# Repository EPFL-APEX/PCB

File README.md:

# APEX PCB's

- Every try you want to experiment in `sandbox/` pls. 
- Keep `main/` for the serious PCB's.
- Add your custom symbols and footprints in `lib/`. Make sure you've added this path to KiCAD, so it can link the libs.

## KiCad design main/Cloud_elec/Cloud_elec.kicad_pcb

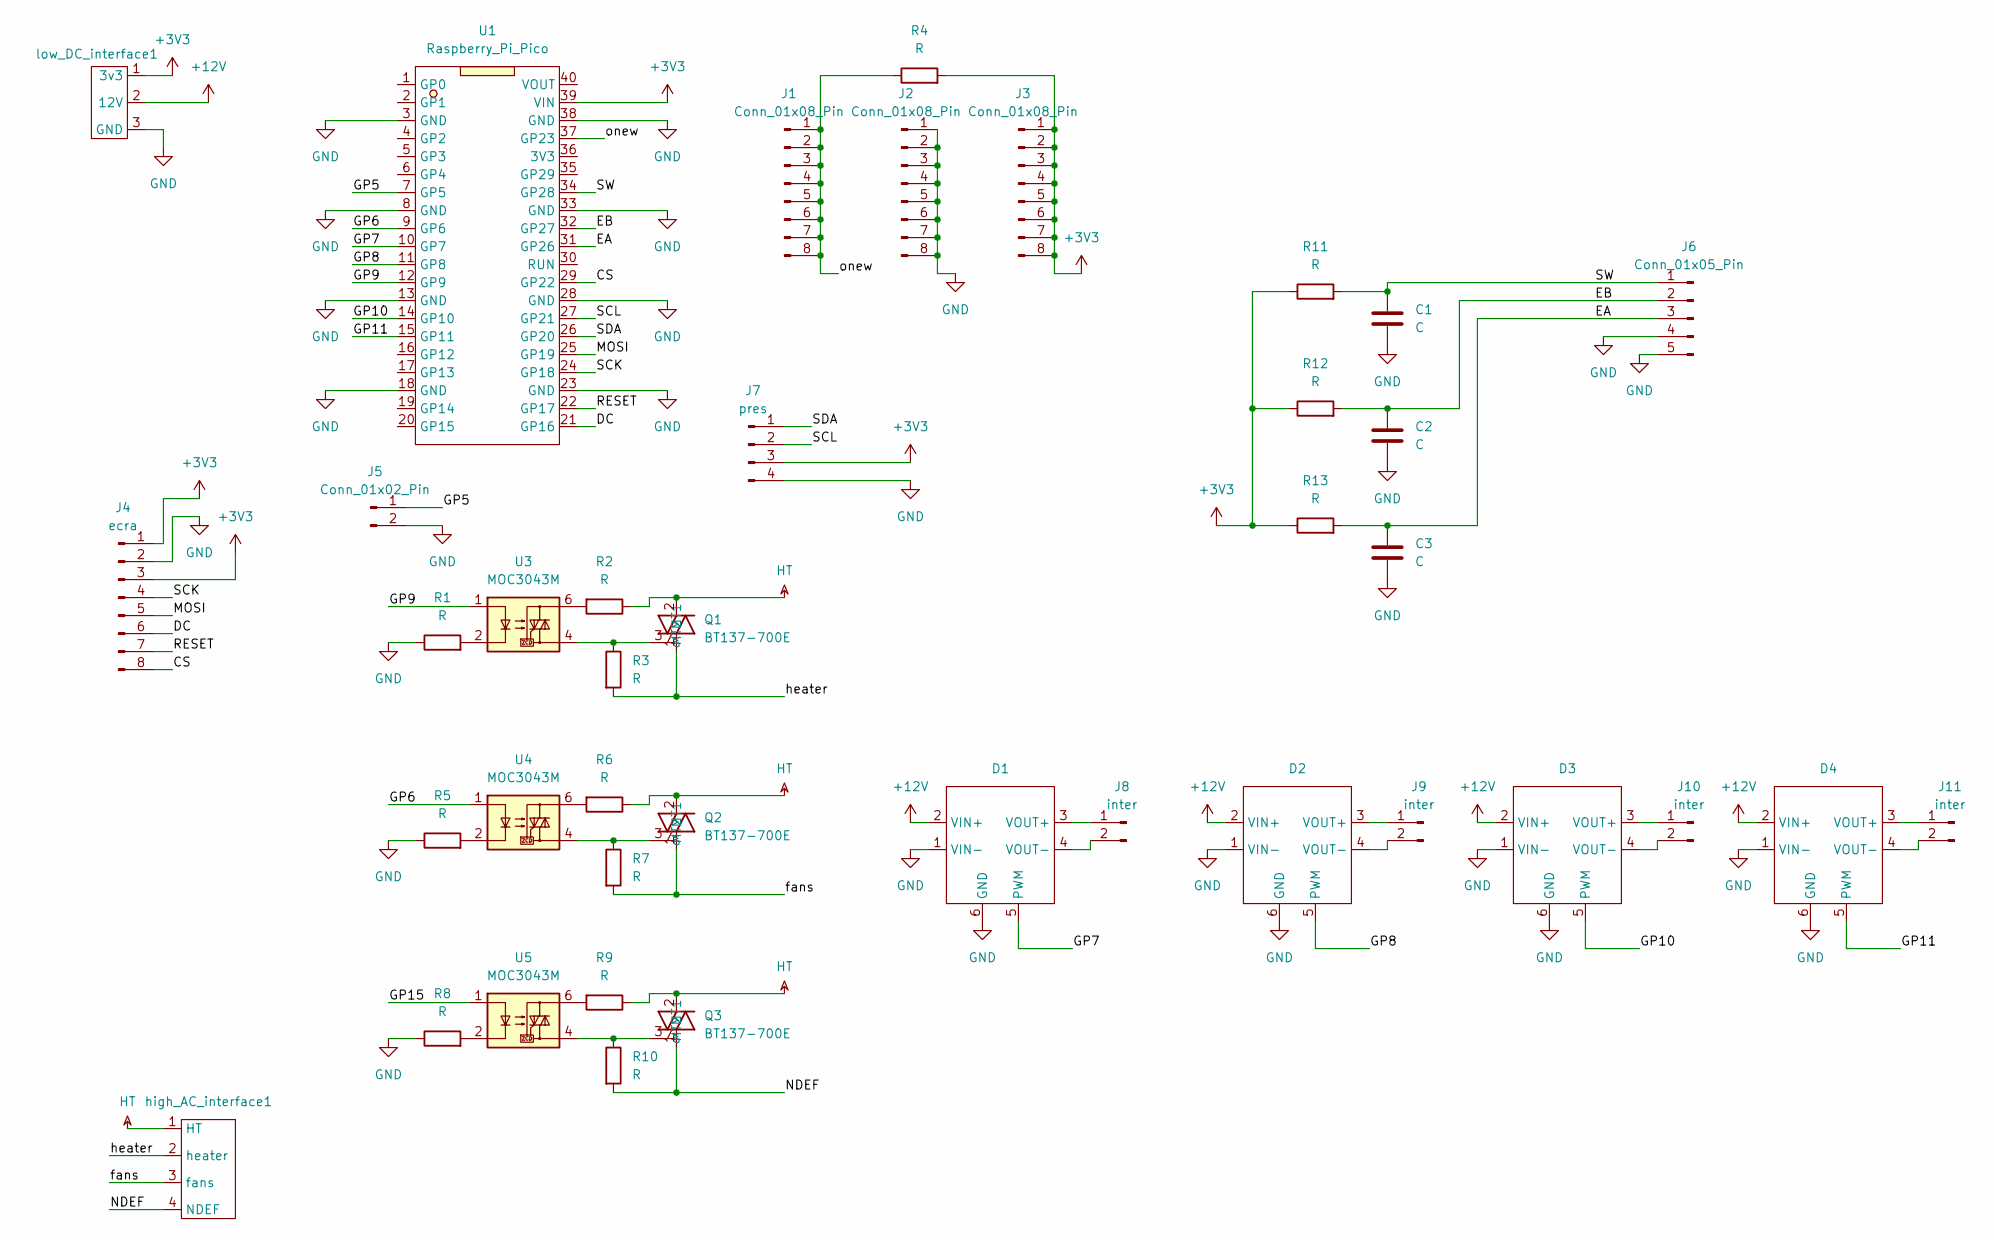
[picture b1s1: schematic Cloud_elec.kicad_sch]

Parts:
C1, C2, C3: C; Capa
D1, D2, D3, D4: Module_D4184
J1, J2, J3: Conn_01x08_Pin; thermosonde
J4: ecra; thermosonde
J5: Conn_01x02_Pin; PinHeader_1x02_P2.54mm_Vertical
J6: Conn_01x05_Pin; PinHeader_1x05_P2.54mm_Vertical
J7: pres; PinHeader_1x04_P2.54mm_Vertical
J8, J9, J10, J11: inter; connecteur2x1_vert
Q1, Q2, Q3: BT137-700E; TO-220-3_Vertical
R1, R2, R3, R4, R5, R6, R7, R8, R9, R10, R11, R12, R13: R; Res
U1: Raspberry_Pi_Pico; RPi_Pico_SMD
U3, U4, U5: MOC3043M; DIP-6_W7.62mm
high_AC_interface1: connecteur4x1_vert
low_DC_interface1: connecteur3x1_vert

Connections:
+3V3: J3.1, J3.2, J3.3, J3.4, J3.5, J3.6, J3.7, J3.8, J4.1, J4.3, J7.3, R4.2, R11.1, R12.1, R13.1, U1.39 (VIN), low_DC_interface1.1 (3v3)
+12V: D1.2 (VIN+), D2.2 (VIN+), D3.2 (VIN+), D4.2 (VIN+), low_DC_interface1.2 (12V)
/CS: J4.8, U1.29 (GP22)
/DC: J4.6, U1.21 (GP16)
/EA: C3.1, J6.3, R13.2, U1.31 (GP26)
/EB: C2.1, J6.2, R12.2, U1.32 (GP27)
/GP5: J5.1, U1.7 (GP5)
/GP6: U1.9 (GP6), U4.1
/GP7: D1.5 (PWM), U1.10 (GP7)
/GP8: D2.5 (PWM), U1.11 (GP8)
/GP9: U1.12 (GP9), U3.1
/GP10: D3.5 (PWM), U1.14 (GP10)
/GP11: D4.5 (PWM), U1.15 (GP11)
/GP15: U5.1
/MOSI: J4.5, U1.25 (GP19)
/NDEF: Q3.1 (MT1), R10.2, high_AC_interface1.4 (NDEF)
/RESET: J4.7, U1.22 (GP17)
/SCK: J4.4, U1.24 (GP18)
/SCL: J7.2, U1.27 (GP21)
/SDA: J7.1, U1.26 (GP20)
/SW: C1.1, J6.1, R11.2, U1.34 (GP28)
/fans: Q2.1 (MT1), R7.2, high_AC_interface1.3 (fans)
/heater: Q1.1 (MT1), R3.2, high_AC_interface1.2 (heater)
/onew: J1.1, J1.2, J1.3, J1.4, J1.5, J1.6, J1.7, J1.8, R4.1, U1.37 (GP23)
GND: C1.2, C2.2, C3.2, D1.1 (VIN-), D1.6 (GND), D2.1 (VIN-), D2.6 (GND), D3.1 (VIN-), D3.6 (GND), D4.1 (VIN-), D4.6 (GND), J2.1, J2.2, J2.3, J2.4, J2.5, J2.6, J2.7, J2.8, J4.2, J5.2, J6.4, J6.5, J7.4, R1.1, R5.1, R8.1, U1.3 (GND), U1.8 (GND), U1.13 (GND), U1.18 (GND), U1.23 (GND), U1.28 (GND), U1.33 (GND), U1.38 (GND), low_DC_interface1.3 (GND)
HT: Q1.2 (MT2), Q2.2 (MT2), Q3.2 (MT2), R2.1, R6.1, R9.1, high_AC_interface1.1 (HT)
unnamed: D1.3 (VOUT+), J8.1
unnamed: D1.4 (VOUT-), J8.2
unnamed: D2.3 (VOUT+), J9.1
unnamed: D2.4 (VOUT-), J9.2
unnamed: D3.3 (VOUT+), J10.1
unnamed: D3.4 (VOUT-), J10.2
unnamed: D4.3 (VOUT+), J11.1
unnamed: D4.4 (VOUT-), J11.2
unnamed: Q1.3 (G), R3.1, U3.4
unnamed: Q2.3 (G), R7.1, U4.4
unnamed: Q3.3 (G), R10.1, U5.4
unnamed: R1.2, U3.2
unnamed: R2.2, U3.6
unnamed: R5.2, U4.2
unnamed: R6.2, U4.6
unnamed: R8.2, U5.2
unnamed: R9.2, U5.6

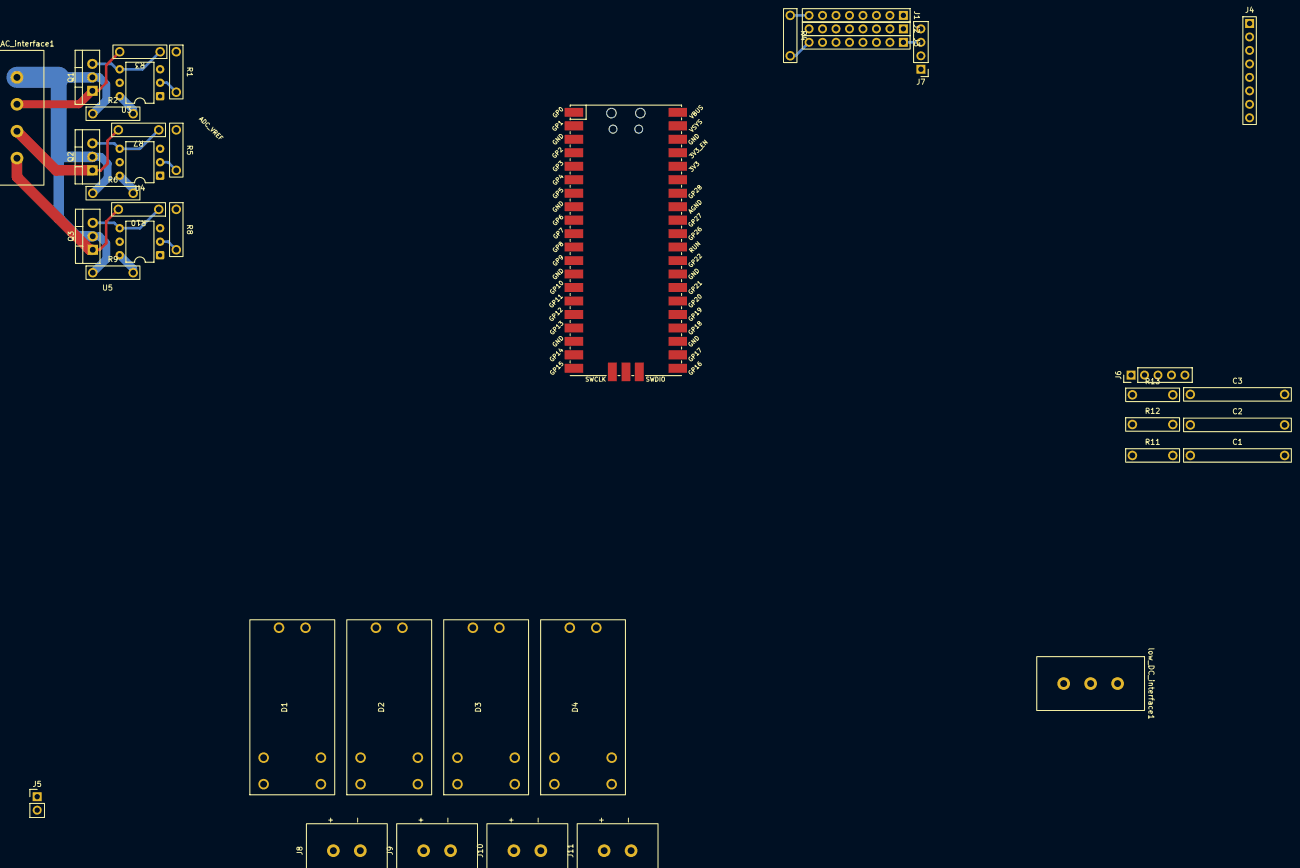
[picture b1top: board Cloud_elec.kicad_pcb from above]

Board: 2 copper layers, 40 parts (0 on the bottom side), 42 nets.
